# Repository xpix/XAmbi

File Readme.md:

XAmbi Network
----------------
By Frank Herrmann (xpixer@gmail.com)
<br/>
XAmbi Network with Atmel Attiny and RFM12B

##Synopsis
The XAmbi Network system are a bunch of Sensor nodes and a Raspberry Gateway. This can control everything in your house and get the data in a nice Webinterface.
This is the Hardware section, here the Software part: [Webinterface](https://github.com/xpix/xambiserver) with MQTT Support. 

What do you need for the first start are follow components:
- a [RaspberryPi](http://en.wikipedia.org/wiki/Raspberry_Pi) with installed [git](http://en.wikipedia.org/wiki/Git_(software))
- a [Jeenode](http://jeelabs.net/projects/hardware/wiki/JeeNode) connected via USB or Serial to RPI
- one or more [xambi sensor](https://github.com/xpix/XAmbi/tree/master/Xambi_kids/xambikid_mainboard) nodes with an RFM12B Transceiver

##Features
- the xambi network system are very modular
- one Gateway with max 999 nodes
- very low bit rate for stable and long range communicaton via [Jeelib](http://jeelabs.net/pub/docs/jeelib/)
- sensor board a kind of breadboard to connect sensors very easy
- Boost to 3.3V on sensor board to get all energy from battery cell
- mainboard very small and standard sizes for normal enclousures

##Examples
- DHT11 [temperature and humidity Sensor](https://github.com/xpix/XAmbi/tree/master/Xambi_kids/xambikid_dht11)
- Dalles DS18B20 [Temperature Sensor](https://github.com/xpix/XAmbi/tree/master/Xambi_kids/xambikid_DS18B20)
- [Mailbox Sensor](https://github.com/xpix/XAmbi/tree/master/Xambi_kids/xambikid_mailbox) via infrared reflection
- Plant [Moisture Sensor](https://github.com/xpix/XAmbi/tree/master/Xambi_kids/xambikid_moisture)

##License
GPL 3.0. See License.txt file.

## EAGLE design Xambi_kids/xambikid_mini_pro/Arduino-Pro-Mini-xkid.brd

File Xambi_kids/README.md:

XAmbi Kids
----------------
By Frank Herrmann (xpixer@gmail.com)
<br/>
XAmbi Network with Atmel Attiny and RFM12B

The XAmbi_Kids are sensors with an Attiny84 and a Transceiver RFM12B or for a cheaper solutuion with a infrared send led. 

##Features:

* small power consumtion. i.e. send every 5min a packet, run 1 year with a CR2032 battery cell
* send via serial with 2400 baud/s
* range up to ~15m in house
* range up to ~80m over the air
* cheap solution
* send via IR LED if you want and a revceiver exists
* small footprint (3x5cm)
* sensorboard with optional booster (1.5V => 3.3V or 5V)

##Hardware:

A xambi kid has 2 PCB's, they are stacked together. I call this [XAmbi-Mainboard](https://github.com/xpix/XAmbi/tree/master/Xambi_kids/xambikid_mainboard) and [XAmbi-Sensorboard](https://github.com/xpix/XAmbi/tree/master/Xambi_kids/xambikid_sensorboard). 
They are designed for a plastik enclouser [PDF Datasheet](https://cdn-reichelt.de/documents/datenblatt/C700/DS_1551G.pdf), they are standard and very cheap ~$2. We have to drill a hole for the antenna and thats all. 

##Software:

- DHT11 [temperature and humidity Sensor](https://github.com/xpix/XAmbi/tree/master/Xambi_kids/xambikid_dht11)
- Dalles DS18B20 [Temperature Sensor](https://github.com/xpix/XAmbi/tree/master/Xambi_kids/xambikid_DS18B20)
- [Mailbox Sensor](https://github.com/xpix/XAmbi/tree/master/Xambi_kids/xambikid_mailbox) via infrared reflection
- Plant [Moisture Sensor](https://github.com/xpix/XAmbi/tree/master/Xambi_kids/xambikid_moisture)

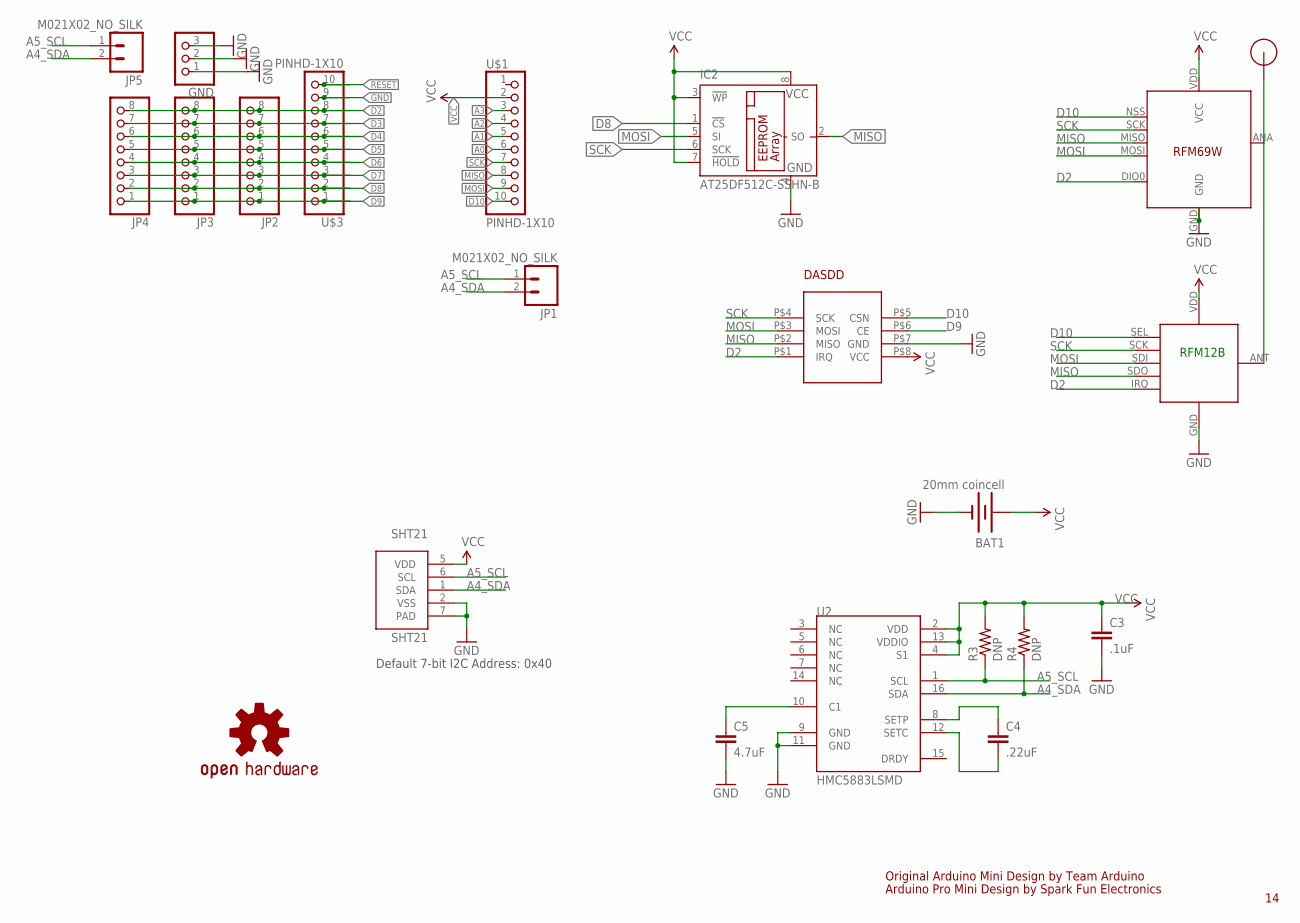
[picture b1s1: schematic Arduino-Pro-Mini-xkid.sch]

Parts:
BAT1: 20mm coincell; BATTCON_20MM_4LEGS
C3: .1uF; 0603-CAP
C4: .22uF; 0603-CAP
C5: 4.7uF; 0603-CAP
DASDD: NRF24L01+_1.27; NRF24L01_1.27
GND: PINHD-1X3; 1X03
IC2: AT25DF512C-SSHN-B; SO-08
JP1, JP5: M021X02_NO_SILK; 1X02_NO_SILK
JP2, JP3, JP4: PINHD-1X8CLEANBIG; 1X08-CLEANBIG
LOGO1: OSHW-LOGOM; OSHW-LOGO-M
R3, R4: DNP; 0603-RES
RFM12B: RFM12B_MINPADS; RFM12B-MINPADS
RFM69W: RFM69; RFM69W-MINPADS
SHT21: SHT21; SEN-SENSIRION-SHT2X
U2: HMC5883LSMD; 16LPCC
U$1, U$3: PINHD-1X10; 1X10-BIG
U$4: RFM12B_ANTENNA; RFM12B-ANTENNA

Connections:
A0: U$1.6
A1: U$1.5
A2: U$1.4
A3: U$1.3
A4_SDA: JP1.2, JP5.2, R4.1, SHT21.1 (SDA), U2.16 (SDA)
A5_SCL: JP1.1, JP5.1, R3.1, SHT21.6 (SCL), U2.1 (SCL)
D2: DASDD.P$1 (IRQ), JP2.8, JP3.8, JP4.8, RFM12B.IRQ, RFM69W.DIO0, U$3.8
D3: JP2.7, JP3.7, JP4.7, U$3.7
D4: JP2.6, JP3.6, JP4.6, U$3.6
D5: JP2.5, JP3.5, JP4.5, U$3.5
D6: JP2.4, JP3.4, JP4.4, U$3.4
D7: JP2.3, JP3.3, JP4.3, U$3.3
D8: IC2.1 (!CS), JP2.2, JP3.2, JP4.2, U$3.2
D9: DASDD.P$6 (CE), JP2.1, JP3.1, JP4.1, U$3.1
D10: DASDD.P$5 (CSN), RFM12B.SEL, RFM69W.NSS (SEL), U$1.10
GND: BAT1.2 (-), C3.2, C5.2, DASDD.P$7 (GND), GND.1, GND.2, GND.3, IC2.4 (GND), RFM12B.GND, RFM69W.GND, SHT21.2 (VSS), SHT21.7 (PAD), U2.9 (GND), U2.11 (GND), U$3.9
MISO: DASDD.P$2 (MISO), IC2.2 (SO), RFM12B.SDO (SDO/MISO), RFM69W.MISO, U$1.8
MOSI: DASDD.P$3 (MOSI), IC2.5 (SI), RFM12B.SDI (SDI/MOSI), RFM69W.MOSI, U$1.9
unnamed: RFM12B.ANT, RFM69W.ANA (ANT), U$4.P$1
unnamed: C4.1, U2.8 (SETP)
unnamed: C4.2, U2.12 (SETC)
unnamed: C5.1, U2.10 (C1)
RESET: U$3.10
SCK: DASDD.P$4 (SCK), IC2.6 (SCK), RFM12B.SCK, RFM69W.SCK, U$1.7
VCC: BAT1.1 (+), C3.1, DASDD.P$8 (VCC), IC2.3 (!WP), IC2.7 (!HOLD), IC2.8 (VCC), R3.2, R4.2, RFM12B.VDD, RFM69W.VDD (VCC), SHT21.5 (VDD), U2.2 (VDD), U2.4 (S1), U2.13 (VDDIO), U$1.2

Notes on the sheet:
Original Arduino Mini Design by Team Arduino
Arduino Pro Mini Design by Spark Fun Electronics
Default 7-bit I2C Address: 0x40
RFM12B

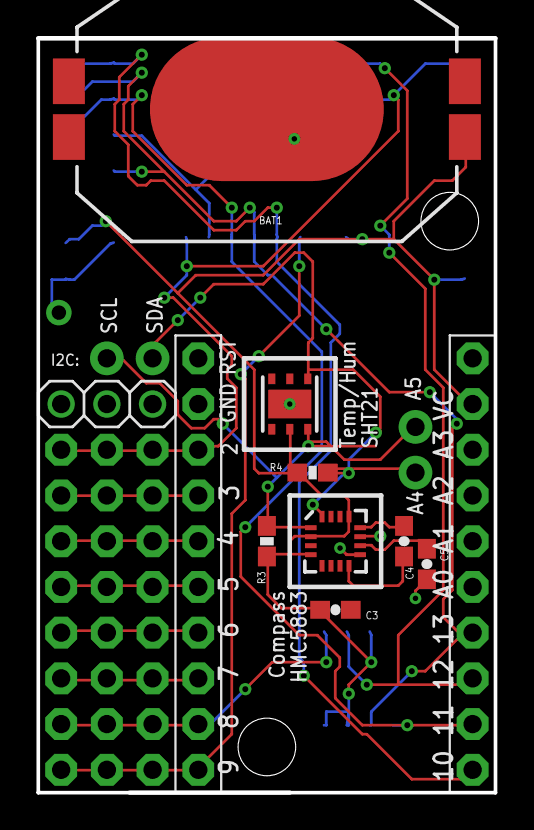
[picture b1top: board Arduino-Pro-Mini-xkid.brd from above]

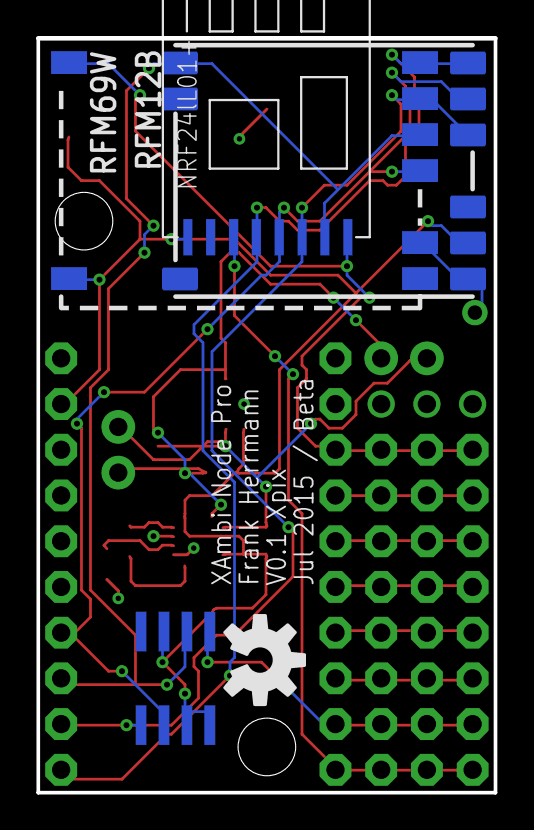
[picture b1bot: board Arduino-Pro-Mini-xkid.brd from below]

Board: 2 copper layers, 25.4 x 41.9 mm, 22 parts (5 on the bottom side), 20 nets.

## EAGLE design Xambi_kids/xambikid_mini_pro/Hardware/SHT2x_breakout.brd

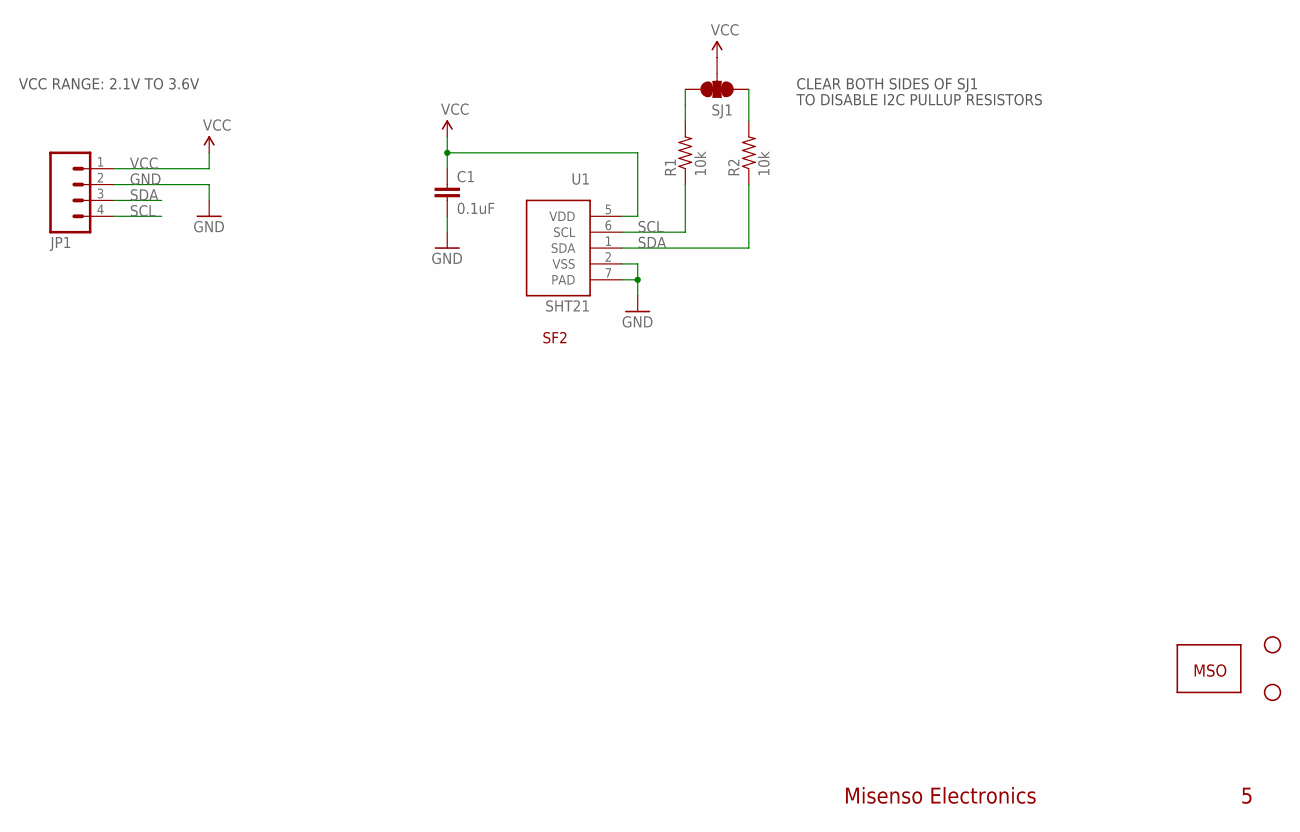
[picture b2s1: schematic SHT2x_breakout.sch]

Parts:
C1: 0.1uF; 0402-CAP
JP1: M04PTH; 1X04
R1, R2: 10k; 0402-RES
SJ1: SOLDERJUMPER_2WAYPASTE1&2&3; SJ_3_PASTE1&2&3
STANDOFF1, STANDOFF2: STAND-OFF
U1: SHT21; SEN-SENSIRION-SHT2X
U$2: MSO-LOGO
U$3: MISC-SENSIRION-SF2

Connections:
GND: C1.2, JP1.2, U1.2 (VSS), U1.7 (PAD)
unnamed: R1.2, SJ1.3
unnamed: R2.2, SJ1.1
SCL: JP1.4, R1.1, U1.6 (SCL)
SDA: JP1.3, R2.1, U1.1 (SDA)
VCC: C1.1, JP1.1, SJ1.2, U1.5 (VDD)

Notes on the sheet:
Misenso Electronics
CLEAR BOTH SIDES OF SJ1
TO DISABLE I2C PULLUP RESISTORS
VCC RANGE: 2.1V TO 3.6V

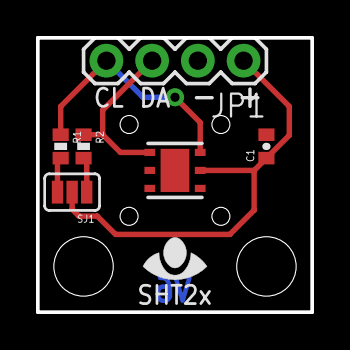
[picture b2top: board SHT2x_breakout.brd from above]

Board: 2 copper layers, 15.2 x 15.2 mm, 10 parts (0 on the bottom side), 6 nets.

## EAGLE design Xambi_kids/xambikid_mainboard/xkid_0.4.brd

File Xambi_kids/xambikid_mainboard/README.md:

XAmbi MainBoard
----------------
By Frank Herrmann (xpixer@gmail.com)
<br/>

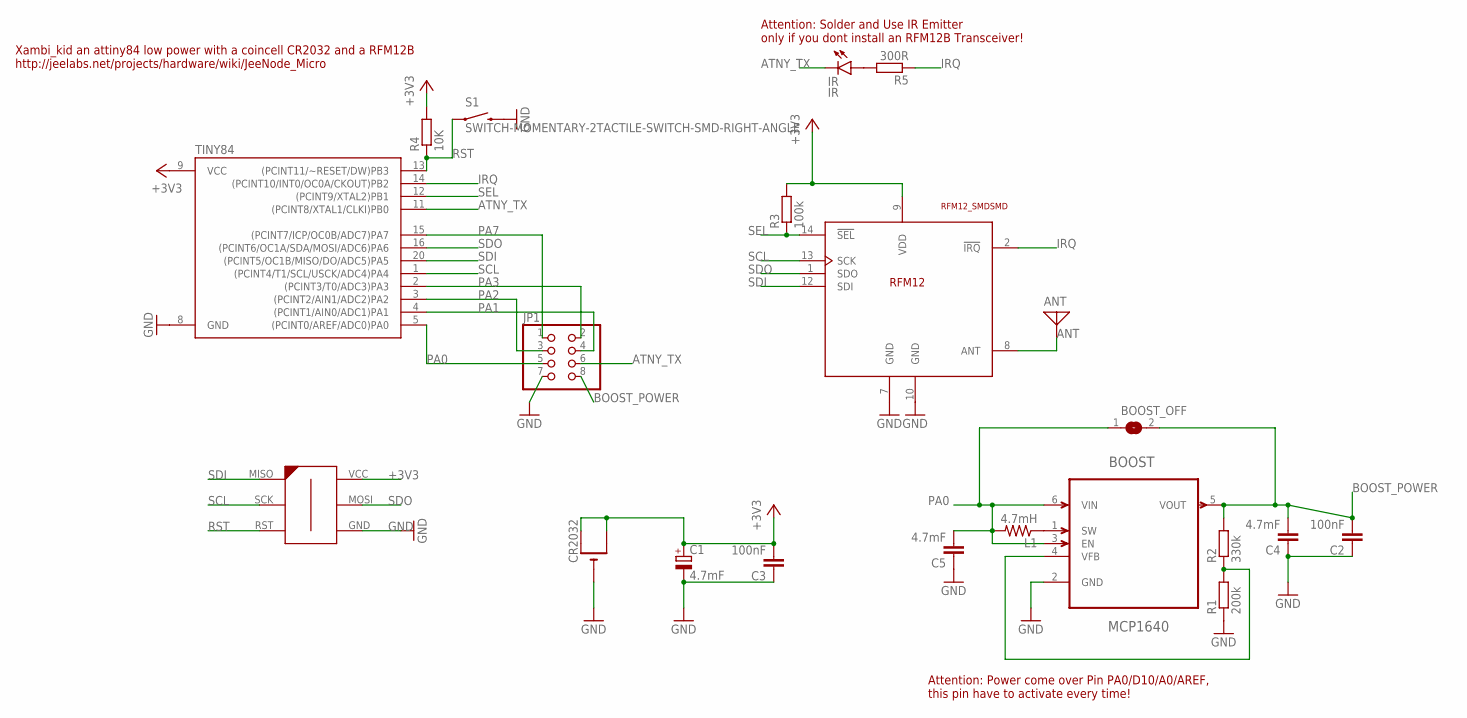
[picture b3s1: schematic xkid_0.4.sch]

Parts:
ANT: ANTENNA; PAD-01
BOOST: MCP1640; SOT95P270X145-6N
BOOST_OFF: SJ
C1: 4.7mF; CT3216
C2, C3: 100nF; C0805K
C4, C5: 4.7mF; C0805K
CR2032: CR2032SMT; CR2032-SMD
IR: IR; LED3MM
JP1: PINHD-2X4_2.54; 2X04
L1: 4.7mH; 0204/5
R1: 200k; R0805
R2: 330k; R0805
R3: 100k; R0805
R4: 10K; R0805
R5: 300R; R0805
S1: SWITCH-MOMENTARY-2TACTILE-SWITCH-SMD-RIGHT-ANGLE; TACTILE_SWITCH-SMD-RIGHT-ANGLE
TINY84: ATTINY84ATTINY84-20MU; QFN20
U$1: RFM12_SMDSMD; RFM12
U$2: AVR-ISP-6-EDGE; 6PAD_ISP

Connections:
+3V3: C1.+, C3.2, CR2032.+$1 (+), CR2032.+$2 (+1), R3.2, R4.2, TINY84.9 (VCC), U$1.9 (VDD), U$2.VCC
ANT: ANT.1, U$1.8 (ANT)
ATNY_TX: IR.K (C), JP1.6, TINY84.11 ((PCINT8/XTAL1/CLKI)PB0)
BOOST_POWER: BOOST.5 (VOUT), BOOST_OFF.2, C2.2, C4.2, JP1.8, R2.2
GND: BOOST.2 (GND), C1.-, C2.1, C3.1, C4.1, C5.1, CR2032.-, JP1.7, R1.1, S1.2, TINY84.8 (GND), U$1.7 (GND), U$1.10 (GND), U$2.GND
IRQ: R5.1, TINY84.14 ((PCINT10/INT0/OC0A/CKOUT)PB2), U$1.2 (!IRQ)
unnamed: IR.A, R5.2
unnamed: BOOST.1 (SW), L1.1
unnamed: BOOST.4 (VFB), R1.2, R2.1
PA0: BOOST.3 (EN), BOOST.6 (VIN), BOOST_OFF.1, C5.2, JP1.5, L1.2, TINY84.5 ((PCINT0/AREF/ADC0)PA0)
PA1: JP1.4, TINY84.4 ((PCINT1/AIN0/ADC1)PA1)
PA2: JP1.3, TINY84.3 ((PCINT2/AIN1/ADC2)PA2)
PA3: JP1.2, TINY84.2 ((PCINT3/T0/ADC3)PA3)
PA7: JP1.1, TINY84.15 ((PCINT7/ICP/OC0B/ADC7)PA7)
RST: R4.1, S1.1, TINY84.13 ((PCINT11/~RESET/DW)PB3), U$2.RST
SCL: TINY84.1 ((PCINT4/T1/SCL/USCK/ADC4)PA4), U$1.13 (SCK), U$2.SCK
SDI: TINY84.20 ((PCINT5/OC1B/MISO/DO/ADC5)PA5), U$1.12 (SDI), U$2.MISO
SDO: TINY84.16 ((PCINT6/OC1A/SDA/MOSI/ADC6)PA6), U$1.1 (SDO), U$2.MOSI
SEL: R3.1, TINY84.12 ((PCINT9/XTAL2)PB1), U$1.14 (!SEL)

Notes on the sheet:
Xambi_kid an attiny84 low power with a coincell CR2032 and a RFM12B http://jeelabs.net/projects/hardware/wiki/JeeNode_Micro
Attention: Solder and Use IR Emitter only if you dont install an RFM12B Transceiver!
Attention: Power come over Pin PA0/D10/A0/AREF, this pin have to activate every time!

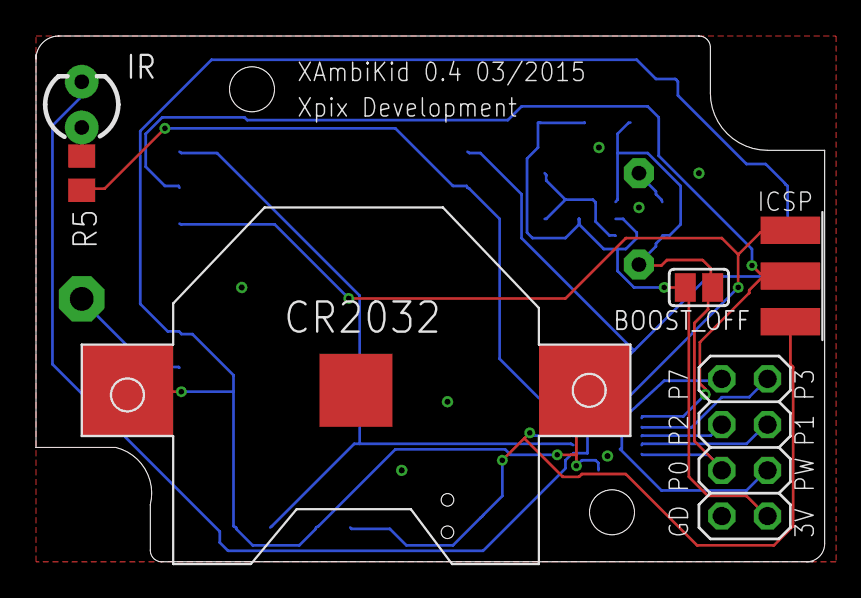
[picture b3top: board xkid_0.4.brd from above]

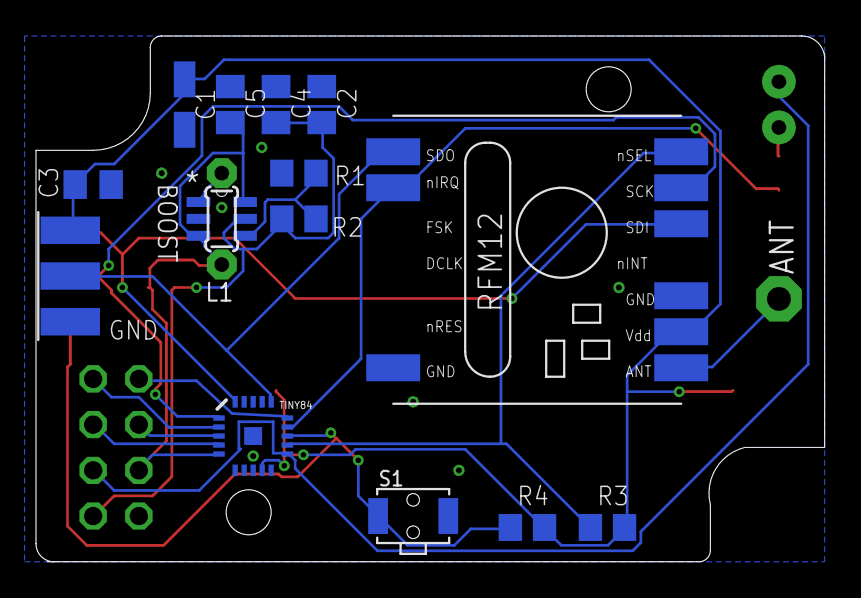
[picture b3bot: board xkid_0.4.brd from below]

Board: 2 copper layers, 43.8 x 29.2 mm, 21 parts (15 on the bottom side), 19 nets.

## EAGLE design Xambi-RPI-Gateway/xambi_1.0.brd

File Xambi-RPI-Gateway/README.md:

XAmbi Gateway for Raspberry PI
----------------
By Frank Herrmann (xpixer@gmail.com)
<br/>
RPI Shield with Atmega329P and RFM12B Transceiver 

Here you find all the design for the Shield, on the pic you see the first Prototype. You can also connect a WS2812 LED Strip to install an Ambilight to your TV. But the first function from this board are a kind of [Jeenode](http://www.digitalsmarties.net/products/jeenode). 

* Solder an RF12B Board and Atmega with Quartz and other Components
* burn the fuses over ISCP and an Bootloader (Arduino UNO) to Atmega: [Tutorial](http://playground.arduino.cc/Learning/Burn168)
* Connect the board with an Raspberry PI
* Use the bootloader and burn the [simple receiver](https://github.com/xpix/XAmbi/tree/master/Xambi_kids/xambikid_simplereceiver) to the XAmbi Board
* connect via screen command and check for the "Init ..." text

You can use this Wiki: http://wiki.openenergymonitor.org/index.php?title=RFM12Pi_V2 they describe very good the steps to burn some firmware to an Arduno clone. This "Xambi-Gateway" are a arduino clone at the internal serial Line from Raspberry.

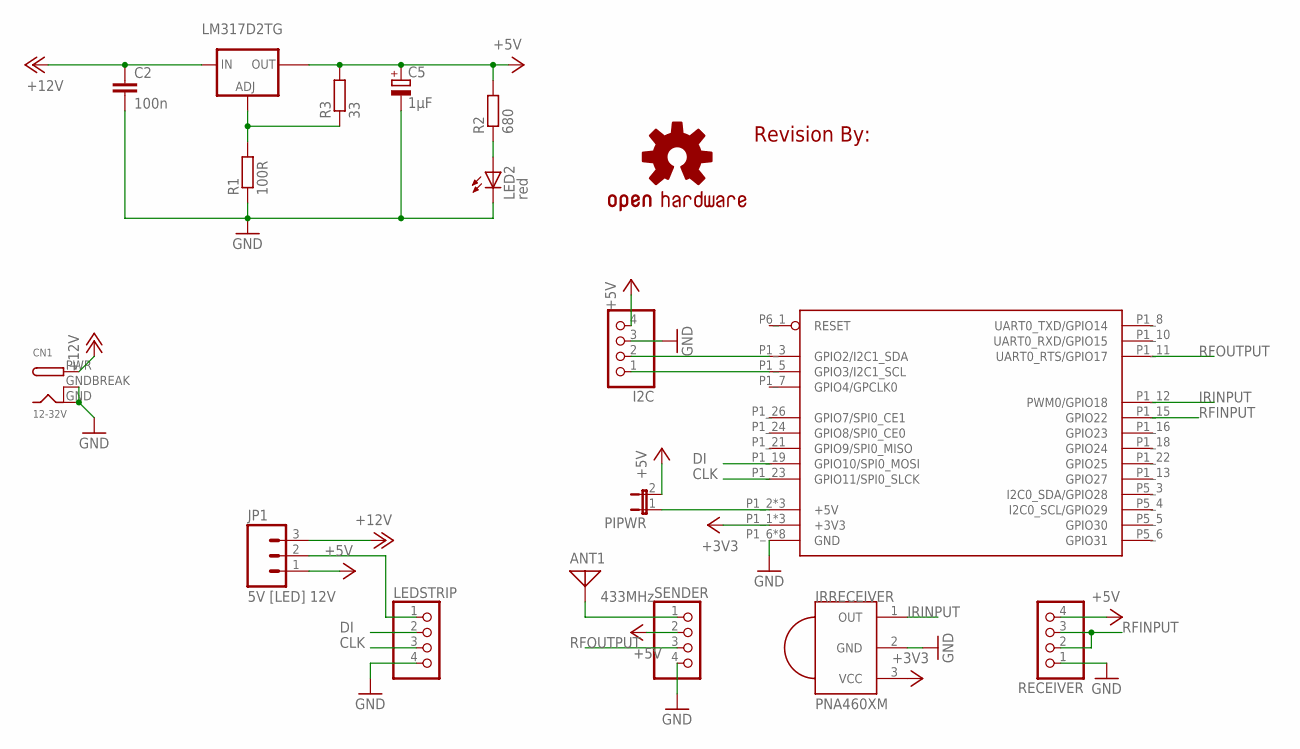
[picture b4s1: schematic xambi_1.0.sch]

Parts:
ANT1: 433MHz; PAD-01
C2: 100n; C1206
C5: 1µF; UD-4X5,8_NICHICON
CN1: 12-32V; DCJACK_2MM_PTH
I2C: PINHD-1X4; 1X04
IRRECEIVER: PNA460XM
JP1: 5V [LED] 12V; 1X03
LED2: red; CHIPLED_1206
LEDSTRIP: PINHD-1X4; 1X04
LM317D2TG: LM1084IS; TO263
LOGO1: OSHW-LOGOS; OSHW-LOGO-S
PIPWR: JP1E; JP1
R1: 100R; R1206
R2: 680; R1206
R3: 33; R1206
RECEIVER: PINHD-1X4; 1X04
SENDER: PINHD-1X4; 1X04
U$2: REVISION
XAMBI_SHIELD_1.0: XPIX Dev. / 2014; RPI-B-V2

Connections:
+3V3: IRRECEIVER.3 (VCC), XAMBI_SHIELD_1.0.P1_1 (+3V3), XAMBI_SHIELD_1.0.P1_17 (+3V3), XAMBI_SHIELD_1.0.P5_2 (+3V3)
+5V: C5.+, I2C.4, JP1.1, LM317D2TG.2 (OUT), PIPWR.2, R2.2, R3.2, RECEIVER.4, SENDER.2
+12V: C2.1, CN1.PWR, JP1.3, LM317D2TG.3 (IN)
CLK: LEDSTRIP.3, XAMBI_SHIELD_1.0.P1_23 (GPIO11/SPI0_SLCK)
DI: LEDSTRIP.2, XAMBI_SHIELD_1.0.P1_19 (GPIO10/SPI0_MOSI)
GND: C2.2, C5.-, CN1.GND, CN1.GNDBREAK, I2C.3, IRRECEIVER.2 (GND), LED2.C, LEDSTRIP.4, R1.1, RECEIVER.1, SENDER.4, XAMBI_SHIELD_1.0.P1_6 (GND), XAMBI_SHIELD_1.0.P1_9 (GND), XAMBI_SHIELD_1.0.P1_14 (GND), XAMBI_SHIELD_1.0.P1_20 (GND), XAMBI_SHIELD_1.0.P1_25 (GND), XAMBI_SHIELD_1.0.P5_7 (GND), XAMBI_SHIELD_1.0.P5_8 (GND), XAMBI_SHIELD_1.0.P6_2 (GND)
GPIO30: XAMBI_SHIELD_1.0.P5_5 (GPIO30)
GPIO31: XAMBI_SHIELD_1.0.P5_6 (GPIO31)
I2C0_SCL/GPIO29: XAMBI_SHIELD_1.0.P5_4 (I2C0_SCL/GPIO29)
I2C0_SDA/GPIO28: XAMBI_SHIELD_1.0.P5_3 (I2C0_SDA/GPIO28)
IRINPUT: IRRECEIVER.1 (OUT), XAMBI_SHIELD_1.0.P1_12 (PWM0/GPIO18)
unnamed: I2C.2, XAMBI_SHIELD_1.0.P1_3 (GPIO2/I2C1_SDA)
unnamed: PIPWR.1, XAMBI_SHIELD_1.0.P1_2 (+5V), XAMBI_SHIELD_1.0.P1_4 (+5V), XAMBI_SHIELD_1.0.P5_1 (+5V)
unnamed: ANT1.1, SENDER.1
unnamed: JP1.2, LEDSTRIP.1
unnamed: I2C.1, XAMBI_SHIELD_1.0.P1_5 (GPIO3/I2C1_SCL)
unnamed: LED2.A, R2.1
unnamed: LM317D2TG.1 (ADJ), R1.2, R3.1
RESET: XAMBI_SHIELD_1.0.P6_1 (RESET)
RFINPUT: RECEIVER.2, RECEIVER.3, XAMBI_SHIELD_1.0.P1_15 (GPIO22)
RFOUTPUT: SENDER.3, XAMBI_SHIELD_1.0.P1_11 (UART0_RTS/GPIO17)

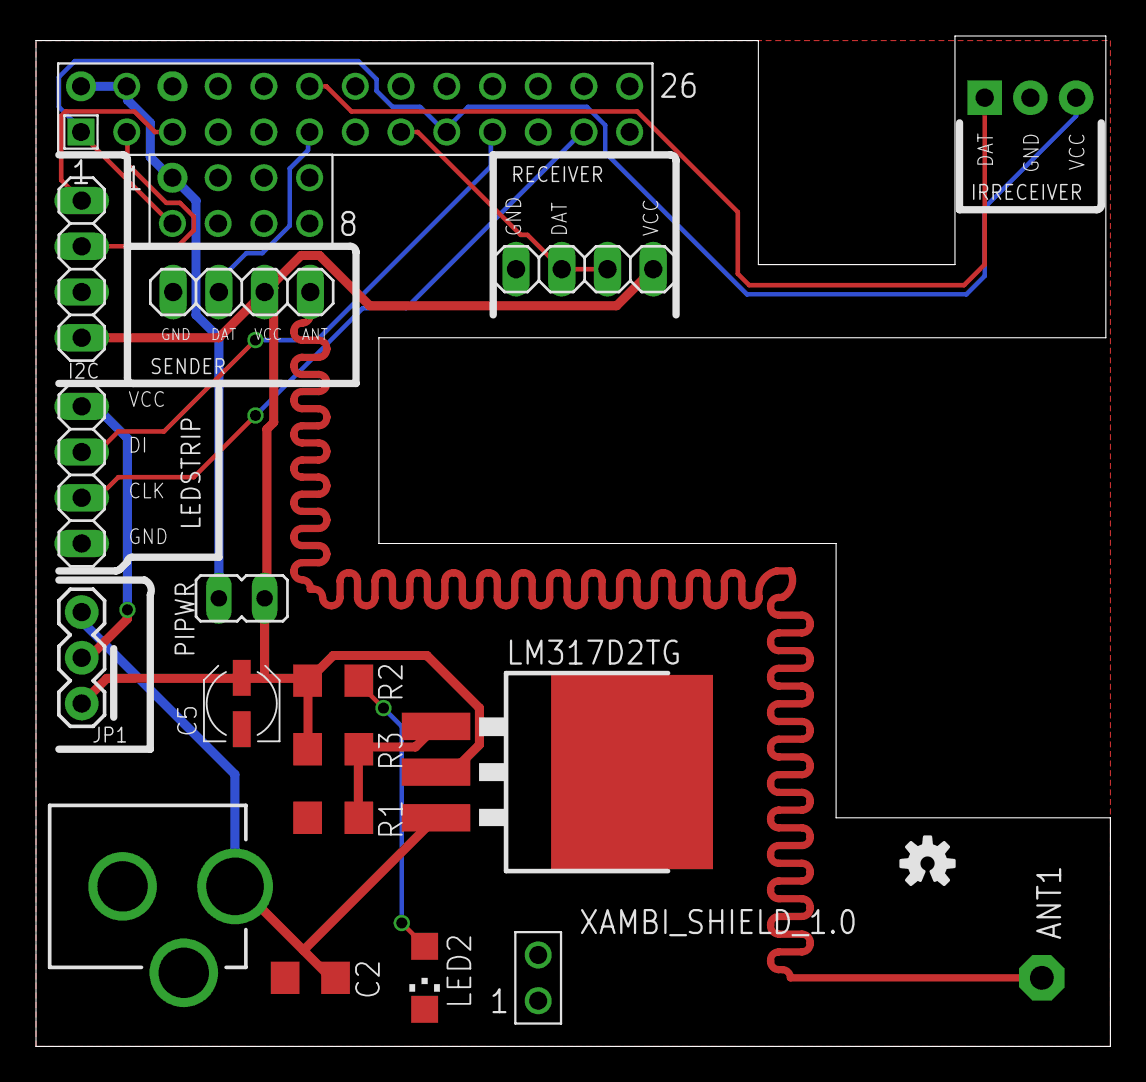
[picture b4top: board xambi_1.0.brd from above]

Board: 2 copper layers, 59.7 x 56.1 mm, 19 parts (1 on the bottom side), 16 nets.

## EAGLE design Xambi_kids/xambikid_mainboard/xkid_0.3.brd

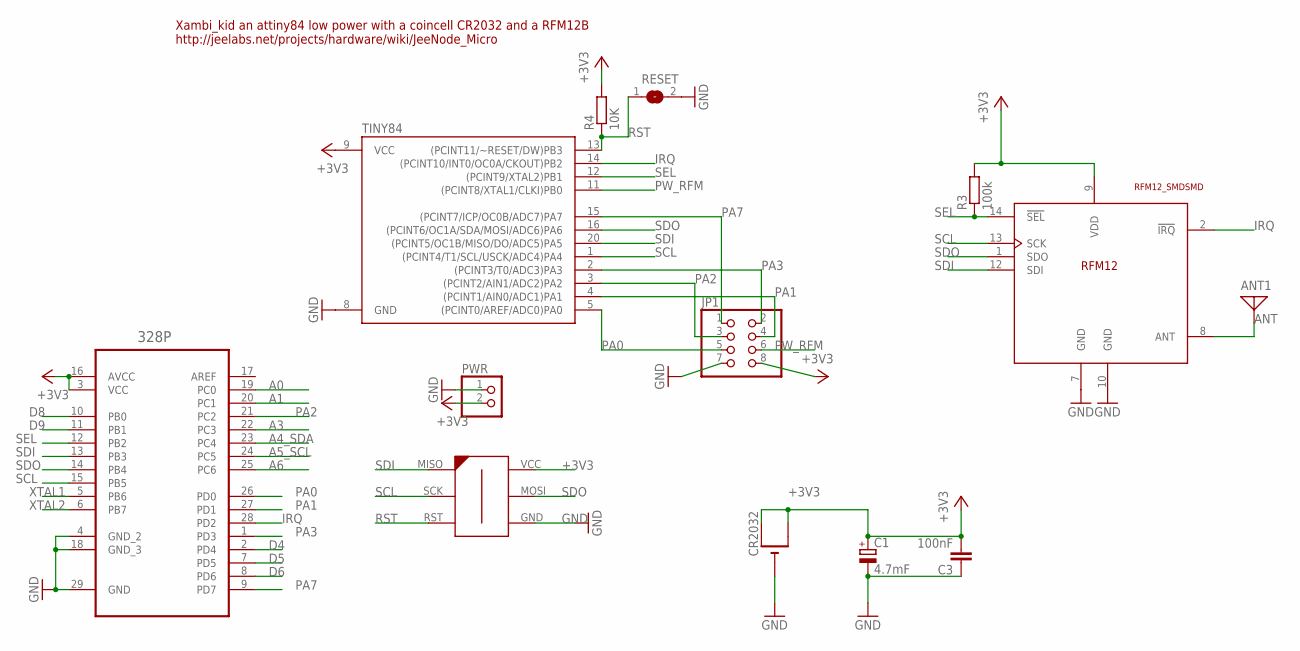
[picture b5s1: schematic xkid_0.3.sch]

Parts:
328P: ATMEGA328P-MMH; QFN45P400X400X100-29N
ANT1: ANTENNA; PAD-01
C1: 4.7mF; CT3216
C3: 100nF; C0805K
CR2032: CR2032SMT; CR2032-SMD
JP1: PINHD-2X4_2.54; 2X04
PWR: PINHD-1X2; 1X02
R3: 100k; R0805
R4: 10K; R0805
RESET: SJ
TINY84: ATTINY84ATTINY84-20MU; QFN20
U$1: RFM12_SMDSMD; RFM12
U$2: AVR-ISP-6-EDGE; 6PAD_ISP

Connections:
+3V3: 328P.3 (VCC), 328P.16 (AVCC), C1.+, C3.2, CR2032.+$1 (+), CR2032.+$2 (+1), JP1.8, PWR.2, R3.2, R4.2, TINY84.9 (VCC), U$1.9 (VDD), U$2.VCC
A0: 328P.19 (PC0)
A1: 328P.20 (PC1)
A3: 328P.22 (PC3)
A4_SDA: 328P.23 (PC4)
A5_SCL: 328P.24 (PC5)
A6: 328P.25 (PC6)
ANT: ANT1.1, U$1.8 (ANT)
D4: 328P.2 (PD4)
D5: 328P.7 (PD5)
D6: 328P.8 (PD6)
D8: 328P.10 (PB0)
D9: 328P.11 (PB1)
GND: 328P.4 (GND_2), 328P.18 (GND_3), 328P.29 (GND), C1.-, C3.1, CR2032.-, JP1.7, PWR.1, RESET.2, TINY84.8 (GND), U$1.7 (GND), U$1.10 (GND), U$2.GND
IRQ: 328P.28 (PD2), TINY84.14 ((PCINT10/INT0/OC0A/CKOUT)PB2), U$1.2 (!IRQ)
PA0: 328P.26 (PD0), JP1.5, TINY84.5 ((PCINT0/AREF/ADC0)PA0)
PA1: 328P.27 (PD1), JP1.4, TINY84.4 ((PCINT1/AIN0/ADC1)PA1)
PA2: 328P.21 (PC2), JP1.3, TINY84.3 ((PCINT2/AIN1/ADC2)PA2)
PA3: 328P.1 (PD3), JP1.2, TINY84.2 ((PCINT3/T0/ADC3)PA3)
PA7: 328P.9 (PD7), JP1.1, TINY84.15 ((PCINT7/ICP/OC0B/ADC7)PA7)
PW_RFM: JP1.6, TINY84.11 ((PCINT8/XTAL1/CLKI)PB0)
RST: R4.1, RESET.1, TINY84.13 ((PCINT11/~RESET/DW)PB3), U$2.RST
SCL: 328P.15 (PB5), TINY84.1 ((PCINT4/T1/SCL/USCK/ADC4)PA4), U$1.13 (SCK), U$2.SCK
SDI: 328P.13 (PB3), TINY84.20 ((PCINT5/OC1B/MISO/DO/ADC5)PA5), U$1.12 (SDI), U$2.MISO
SDO: 328P.14 (PB4), TINY84.16 ((PCINT6/OC1A/SDA/MOSI/ADC6)PA6), U$1.1 (SDO), U$2.MOSI
SEL: 328P.12 (PB2), R3.1, TINY84.12 ((PCINT9/XTAL2)PB1), U$1.14 (!SEL)
XTAL1: 328P.5 (PB6)
XTAL2: 328P.6 (PB7)

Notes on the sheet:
Xambi_kid an attiny84 low power with a coincell CR2032 and a RFM12B http://jeelabs.net/projects/hardware/wiki/JeeNode_Micro

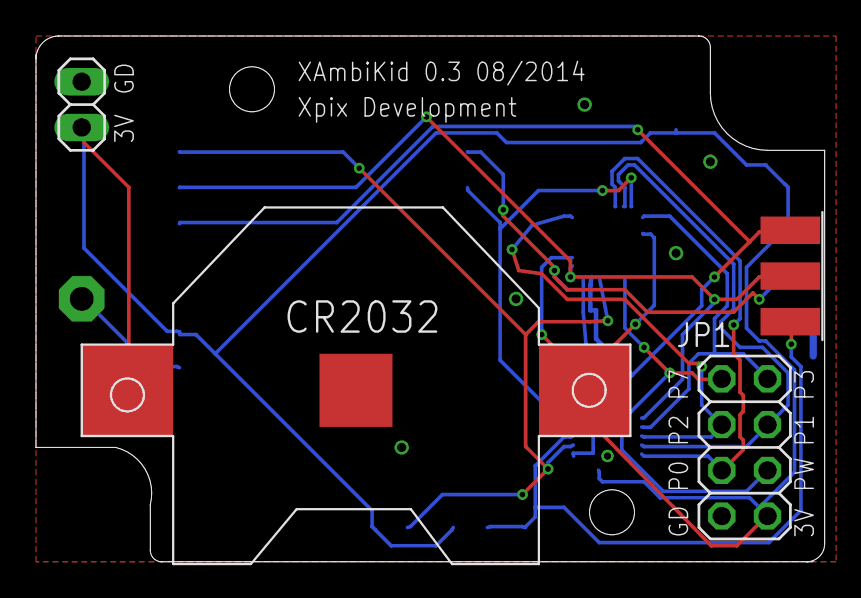
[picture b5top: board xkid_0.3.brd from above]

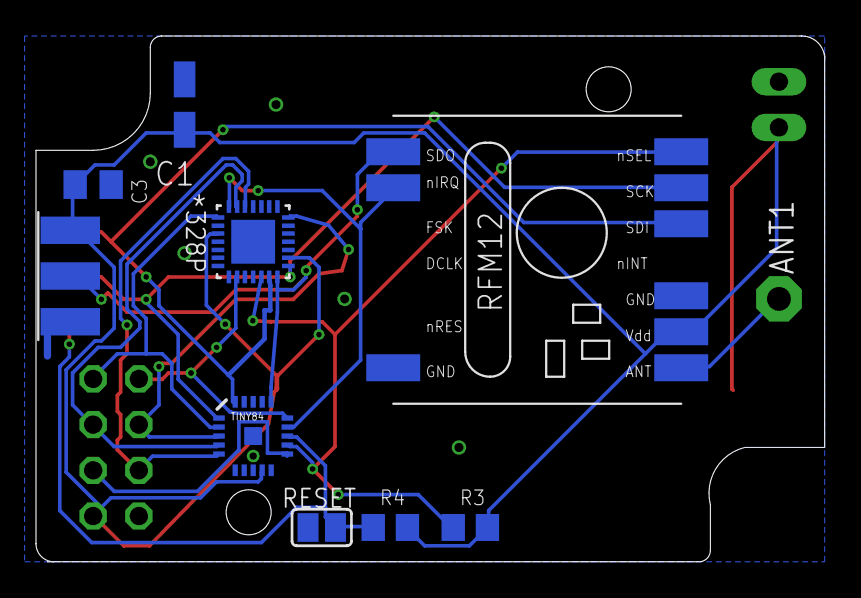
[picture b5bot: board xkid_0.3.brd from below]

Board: 2 copper layers, 43.8 x 29.2 mm, 13 parts (9 on the bottom side), 15 nets.

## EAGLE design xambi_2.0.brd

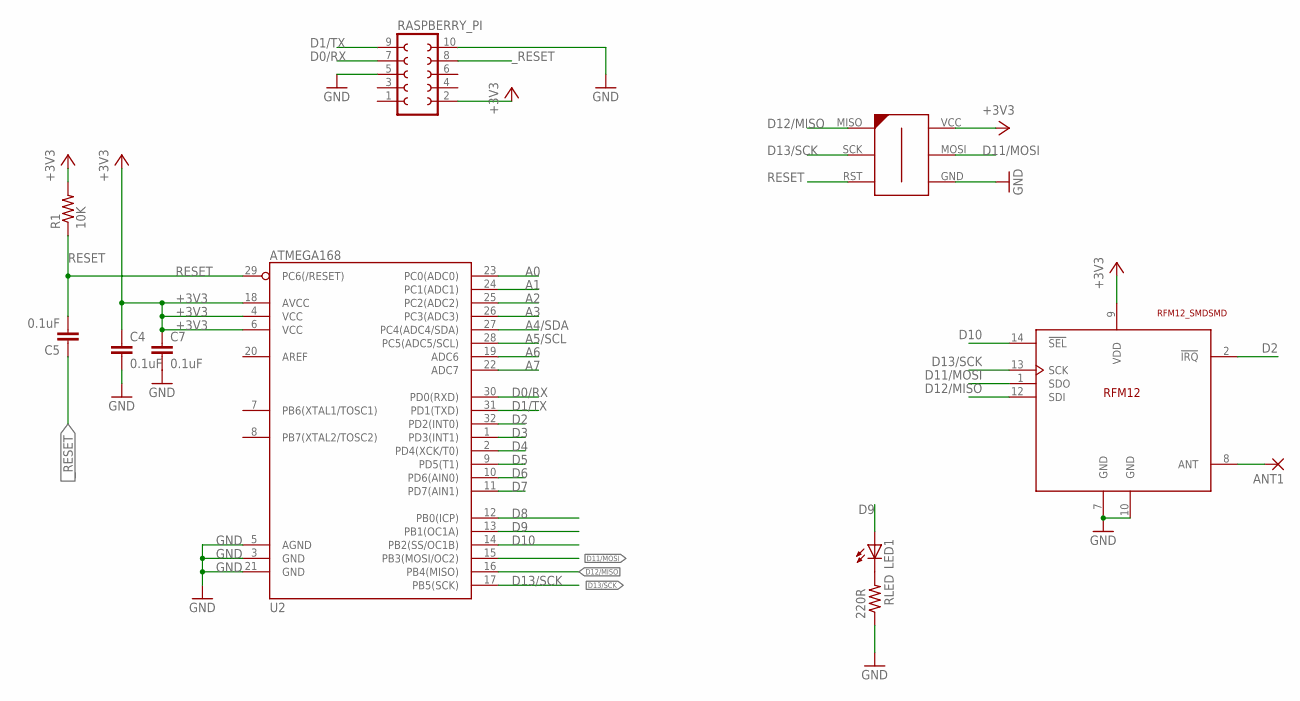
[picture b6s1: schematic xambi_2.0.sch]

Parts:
ANT1: 1,6/0,8
C4, C5, C7: 0.1uF; C0603
ICSP: AVR-ISP-6-EDGE; 6PAD_ISP
LED1: LEDSML0805; SML0805
R1: 10K; R0603
RASPBERRY_PI: FE05-2
RLED: 220R; R0805
U2: ATMEGA168; TQFP32-08
U$1: RFM12_SMDSMD; RFM12

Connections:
+3V3: C4.1, C7.1, ICSP.VCC, R1.2, RASPBERRY_PI.2, U2.4 (VCC), U2.6 (VCC), U2.18 (AVCC), U$1.9 (VDD)
A0: U2.23 (PC0(ADC0))
A1: U2.24 (PC1(ADC1))
A2: U2.25 (PC2(ADC2))
A3: U2.26 (PC3(ADC3))
A4/SDA: U2.27 (PC4(ADC4/SDA))
A5/SCL: U2.28 (PC5(ADC5/SCL))
A6: U2.19 (ADC6)
A7: U2.22 (ADC7)
D0/RX: RASPBERRY_PI.7, U2.30 (PD0(RXD))
D1/TX: RASPBERRY_PI.9, U2.31 (PD1(TXD))
D2: U2.32 (PD2(INT0)), U$1.2 (!IRQ)
D3: U2.1 (PD3(INT1))
D4: U2.2 (PD4(XCK/T0))
D5: U2.9 (PD5(T1))
D6: U2.10 (PD6(AIN0))
D7: U2.11 (PD7(AIN1))
D8: U2.12 (PB0(ICP))
D9: LED1.A, U2.13 (PB1(OC1A))
D10: U2.14 (PB2(SS/OC1B)), U$1.14 (!SEL)
D11/MOSI: ICSP.MOSI, U2.15 (PB3(MOSI/OC2)), U$1.1 (SDO)
D12/MISO: ICSP.MISO, U2.16 (PB4(MISO)), U$1.12 (SDI)
D13/SCK: ICSP.SCK, U2.17 (PB5(SCK)), U$1.13 (SCK)
GND: C4.2, C7.2, ICSP.GND, RASPBERRY_PI.5, RASPBERRY_PI.10, RLED.1, U2.3 (GND), U2.5 (AGND), U2.21 (GND), U$1.7 (GND), U$1.10 (GND)
unnamed: LED1.C, RLED.2
unnamed: ANT1.1, U$1.8 (ANT)
RESET: C5.2, ICSP.RST, R1.1, U2.29 (PC6(/RESET))
_RESET: C5.1, RASPBERRY_PI.8

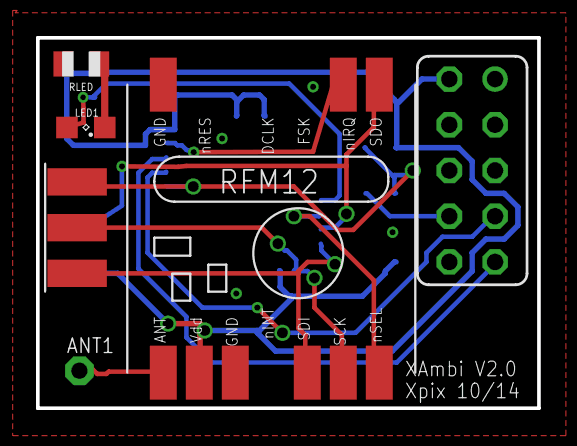
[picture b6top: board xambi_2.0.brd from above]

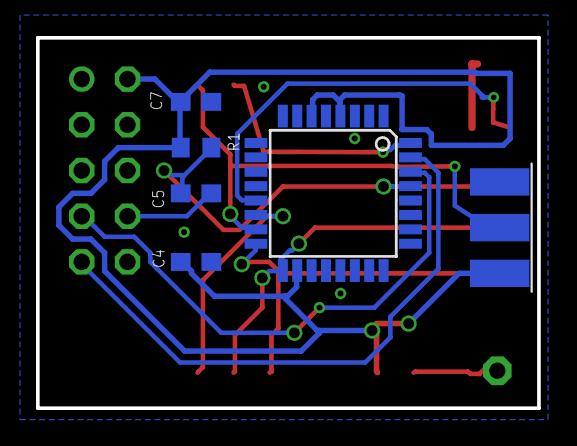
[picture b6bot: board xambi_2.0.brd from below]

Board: 2 copper layers, 27.8 x 20.6 mm, 11 parts (5 on the bottom side), 14 nets.

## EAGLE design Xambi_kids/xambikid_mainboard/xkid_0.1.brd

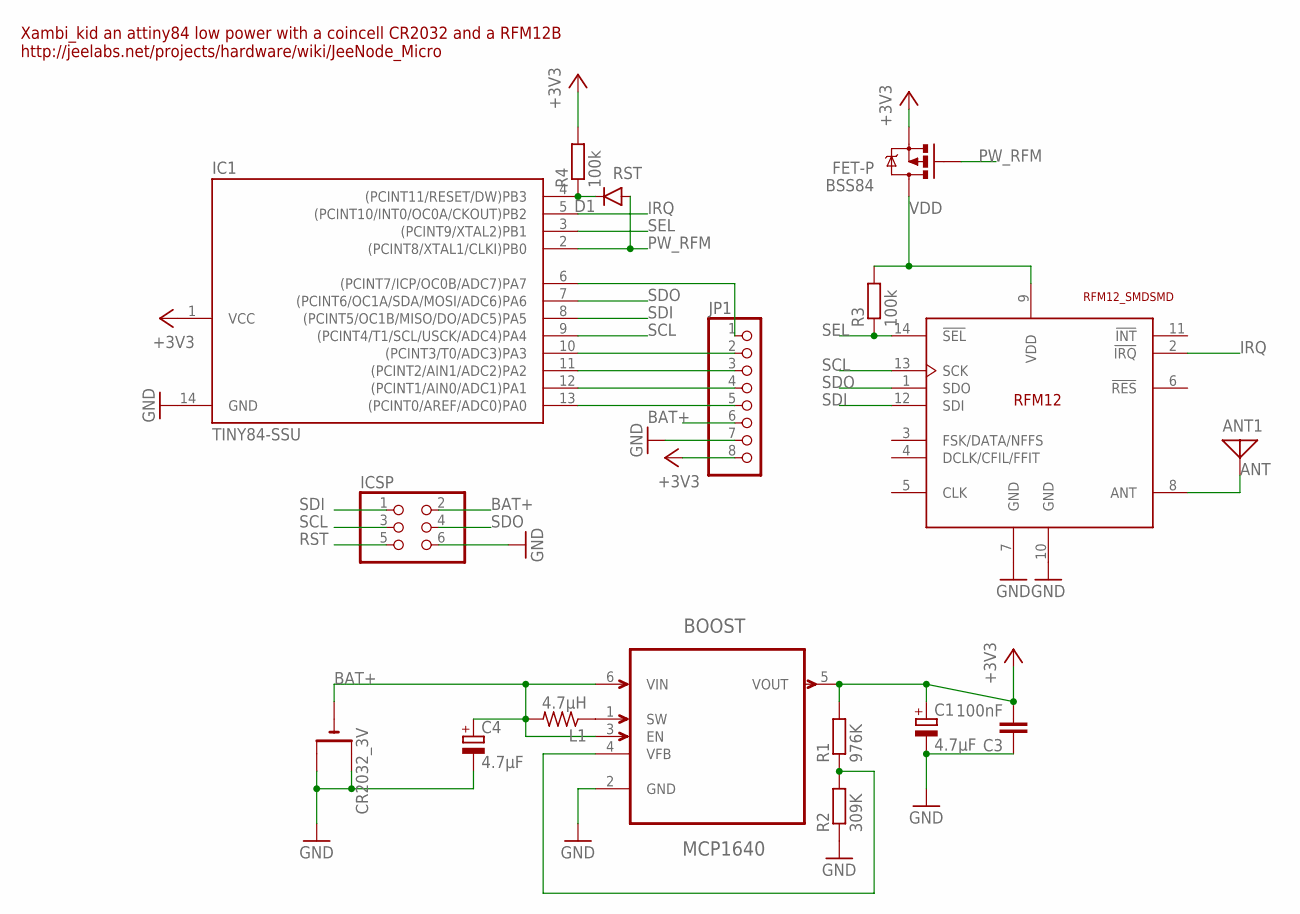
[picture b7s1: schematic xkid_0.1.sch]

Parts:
ANT1: ANTENNA; PAD-01
BOOST: MCP1640; SOT95P270X145-6N
BSS84: FET-P; SOT23-3
C1, C4: 4.7μF; CT3216
C3: 100nF; C0805K
CR2032_3V: CR2032THM; CR2032-THRU
D1: DIODESOD; SOD-323
IC1: TINY84-SSU; SOIC14
ICSP: PINHD-2X3; 2X03
JP1: PINHD-1X8LOCK; 1X08-LOCK
L1: 4.7μH; 0204/5
R1: 976K; R0805
R2: 309K; R0805
R3, R4: 100k; R0805
U$1: RFM12_SMDSMD; RFM12

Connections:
+3V3: BOOST.5 (VOUT), BSS84.2 (S), C1.+, C3.2, IC1.1 (VCC), JP1.8, R1.2, R4.2
ANT: ANT1.1, U$1.8 (ANT)
BAT+: BOOST.3 (EN), BOOST.6 (VIN), C4.+, CR2032_3V.-, ICSP.2, JP1.6, L1.2
GND: BOOST.2 (GND), C1.-, C3.1, C4.-, CR2032_3V.+1 (+), CR2032_3V.+2 (+1), IC1.14 (GND), ICSP.6, JP1.7, R2.1, U$1.7 (GND), U$1.10 (GND)
IRQ: IC1.5 ((PCINT10/INT0/OC0A/CKOUT)PB2), U$1.2 (!IRQ)
unnamed: BOOST.1 (SW), L1.1
unnamed: BOOST.4 (VFB), R1.1, R2.2
unnamed: IC1.6 ((PCINT7/ICP/OC0B/ADC7)PA7), JP1.1
unnamed: IC1.10 ((PCINT3/T0/ADC3)PA3), JP1.2
unnamed: IC1.11 ((PCINT2/AIN1/ADC2)PA2), JP1.3
unnamed: IC1.12 ((PCINT1/AIN0/ADC1)PA1), JP1.4
unnamed: IC1.13 ((PCINT0/AREF/ADC0)PA0), JP1.5
PW_RFM: BSS84.1 (G), D1.A, IC1.2 ((PCINT8/XTAL1/CLKI)PB0)
RST: D1.C, IC1.4 ((PCINT11/RESET/DW)PB3), ICSP.5, R4.1
SCL: IC1.9 ((PCINT4/T1/SCL/USCK/ADC4)PA4), ICSP.3, U$1.13 (SCK)
SDI: IC1.8 ((PCINT5/OC1B/MISO/DO/ADC5)PA5), ICSP.1, U$1.12 (SDI)
SDO: IC1.7 ((PCINT6/OC1A/SDA/MOSI/ADC6)PA6), ICSP.4, U$1.1 (SDO)
SEL: IC1.3 ((PCINT9/XTAL2)PB1), R3.1, U$1.14 (!SEL)
VDD: BSS84.3 (D), R3.2, U$1.9 (VDD)

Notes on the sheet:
Xambi_kid an attiny84 low power with a coincell CR2032 and a RFM12B http://jeelabs.net/projects/hardware/wiki/JeeNode_Micro

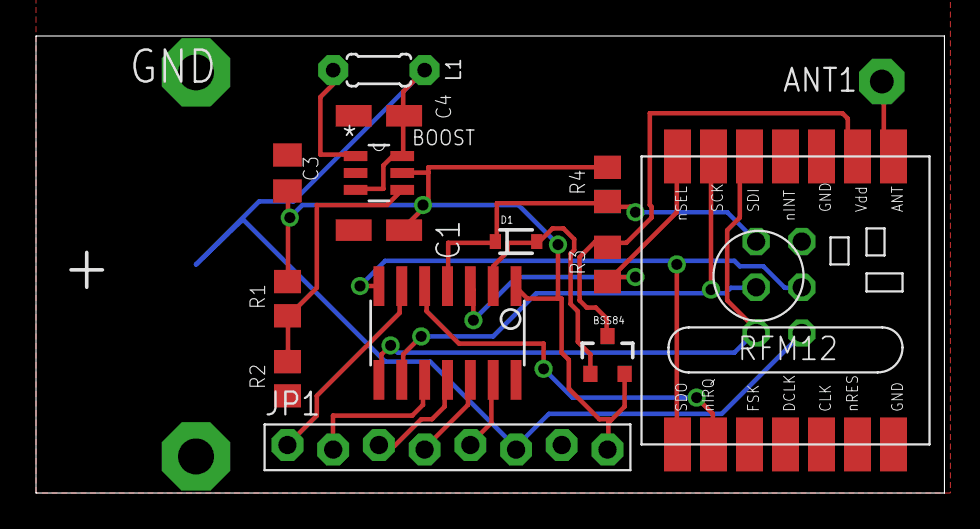
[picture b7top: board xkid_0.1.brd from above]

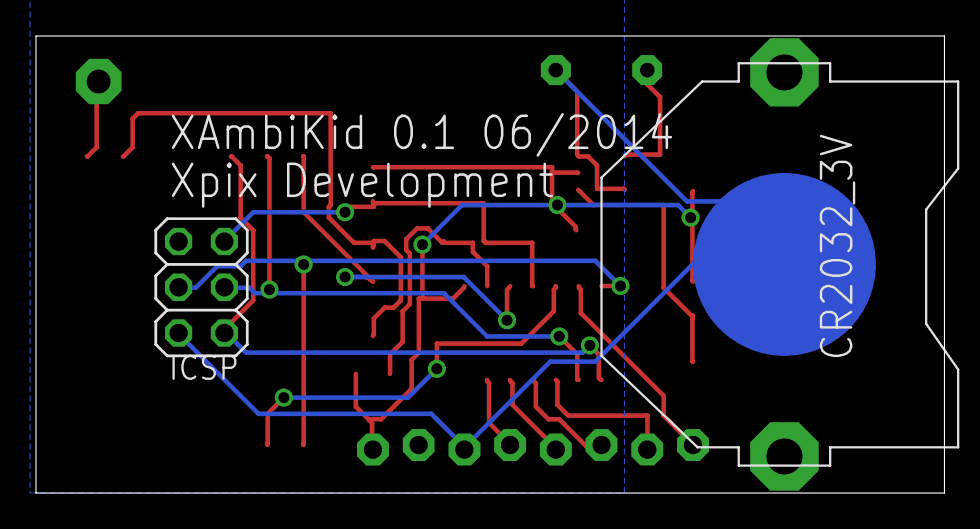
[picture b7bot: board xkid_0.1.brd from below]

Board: 2 copper layers, 50.5 x 25.4 mm, 17 parts (2 on the bottom side), 19 nets.

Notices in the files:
parts and their libraries:
raspberry: This library stands under the CERN Open Hardware Licence.
SparkFun-Aesthetics: Licensing: Creative Commons ShareAlike 4.0 International - https://creativecommons.org/licenses/by-sa/4.0
SparkFun-Aesthetics: Released under the Creative Commons
